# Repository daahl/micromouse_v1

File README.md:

# Micromouse_v1

This project aims to develop a [micromouse](https://www.youtube.com/results?search_query=micromouse) using a DOIT ESP32 dev module. The robot is powered by two 18620 batteries in series, and two micro metal motors fitted with encoders. The mapping is done using three VL53L0X TOF sensors.

**Currently a work in progress.**

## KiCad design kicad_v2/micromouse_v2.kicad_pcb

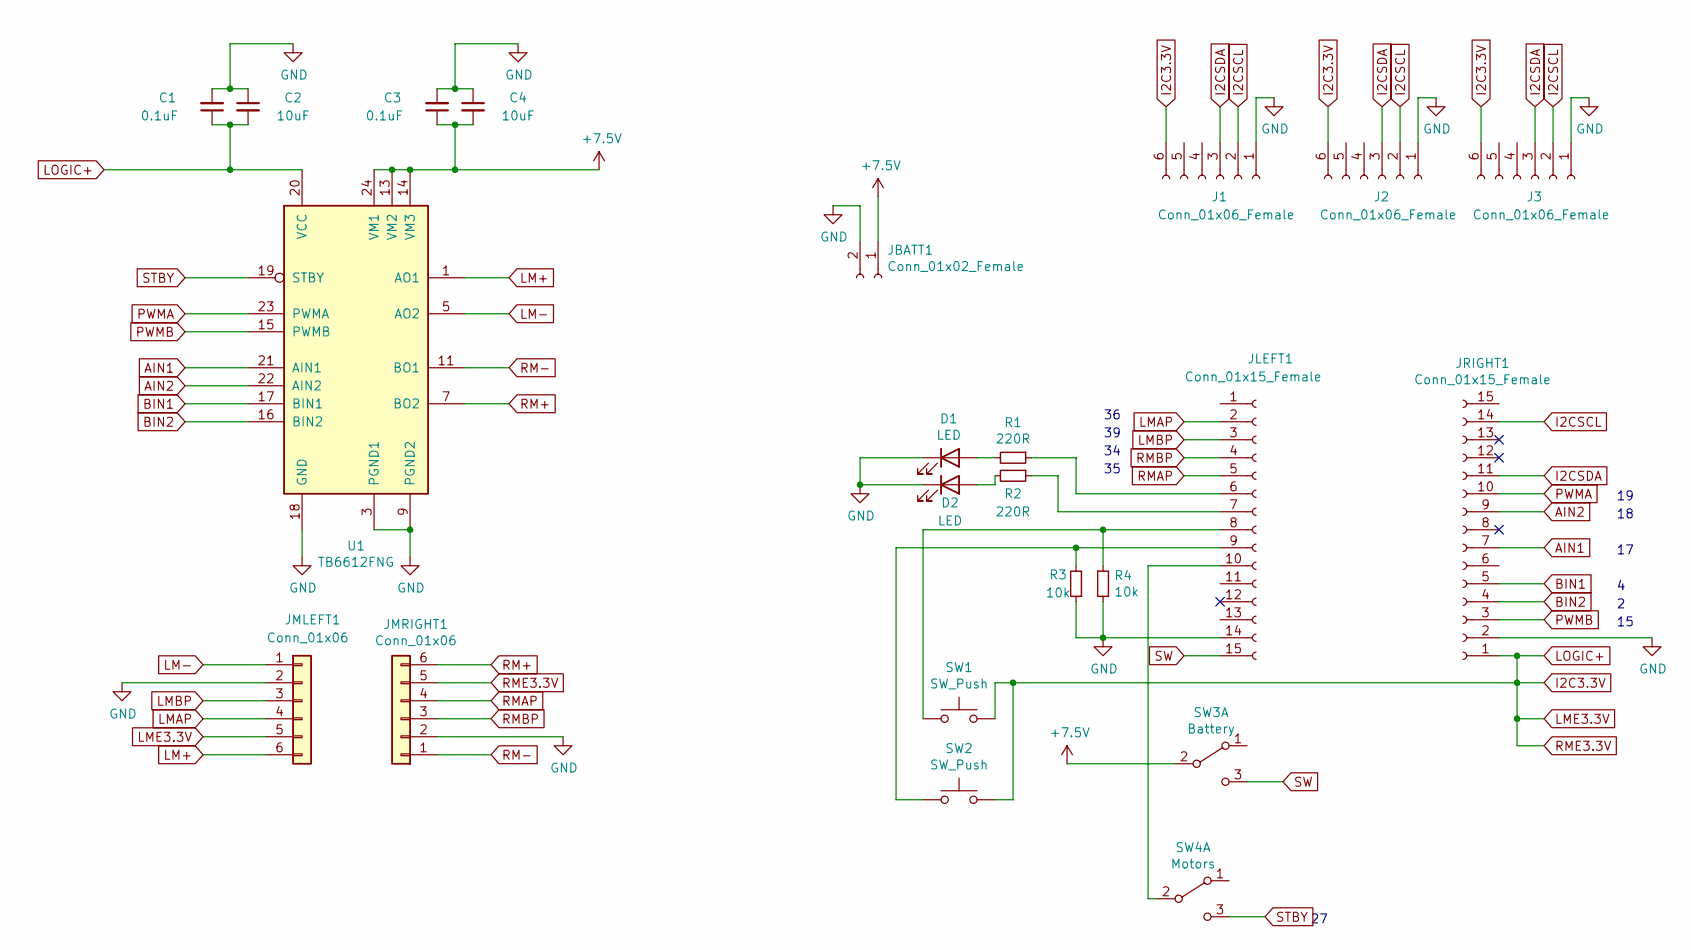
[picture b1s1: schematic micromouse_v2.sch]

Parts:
C1, C3: 0.1uF; C_0603_1608Metric_Pad1.08x0.95mm_HandSolder
C2, C4: 10uF; C_0603_1608Metric_Pad1.08x0.95mm_HandSolder
D1, D2: LED; LED_0603_1608Metric_Pad1.05x0.95mm_HandSolder
J1, J2, J3: Conn_01x06_Female; PinSocket_1x06_P2.54mm_Vertical
JBATT1: Conn_01x02_Female; JST_EH_B2B-EH-A_1x02_P2.50mm_Vertical
JLEFT1: Conn_01x15_Female; PinSocket_1x15_P2.54mm_Vertical
JMLEFT1: Conn_01x06; JST_EH_B6B-EH-A_1x06_P2.50mm_Vertical
JMRIGHT1: Conn_01x06; JST_EH_B6B-EH-A_1x06_P2.50mm_Vertical
JRIGHT1: Conn_01x15_Female; PinSocket_1x15_P2.54mm_Vertical
R1, R2: 220R; R_0603_1608Metric_Pad0.98x0.95mm_HandSolder
R3, R4: 10k; R_0603_1608Metric_Pad0.98x0.95mm_HandSolder
SW1, SW2: SW_Push; SW_SPST_Omron_B3FS-100xP
SW3: Battery; SW_CuK_OS102011MA1QN1_SPDT_Angled
SW4: Motors; SW_CuK_OS102011MA1QN1_SPDT_Angled
U1: TB6612FNG; SSOP-24_5.3x8.2mm_P0.65mm

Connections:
+7.5V: C3.1, C4.2, JBATT1.1, SW3.2 (B), U1.13 (VM2), U1.14 (VM3), U1.24 (VM1)
AIN1: JRIGHT1.7, U1.21 (AIN1)
AIN2: JRIGHT1.9, U1.22 (AIN2)
BIN1: JRIGHT1.5, U1.17 (BIN1)
BIN2: JRIGHT1.4, U1.16 (BIN2)
GND: C1.2, C2.1, C3.2, C4.1, D1.1 (K), D2.1 (K), J1.1, J2.1, J3.1, JBATT1.2, JLEFT1.14, JMLEFT1.2, JMRIGHT1.2, JRIGHT1.2, R3.1, R4.2, U1.3 (PGND1), U1.4 (PGND1), U1.9 (PGND2), U1.10 (PGND2), U1.18 (GND)
I2C3.3V: C1.1, C2.2, J1.6, J2.6, J3.6, JMLEFT1.5, JMRIGHT1.5, JRIGHT1.1, SW1.2, SW2.2, U1.20 (VCC)
I2CSCL: J1.2, J2.2, J3.2, JRIGHT1.14
I2CSDA: J1.3, J2.3, J3.3, JRIGHT1.11
LM+: JMLEFT1.6, U1.1 (AO1), U1.2 (AO1)
LM-: JMLEFT1.1, U1.5 (AO2), U1.6 (AO2)
LMAP: JLEFT1.2, JMLEFT1.4
LMBP: JLEFT1.3, JMLEFT1.3
unnamed: D1.2 (A), R1.2
unnamed: D2.2 (A), R2.2
unnamed: JLEFT1.6, R1.1
unnamed: JLEFT1.7, R2.1
unnamed: JLEFT1.8, R4.1, SW1.1
unnamed: JLEFT1.9, R3.2, SW2.1
unnamed: JLEFT1.10, SW4.2 (B)
PWMA: JRIGHT1.10, U1.23 (PWMA)
PWMB: JRIGHT1.3, U1.15 (PWMB)
RM+: JMRIGHT1.6, U1.7 (BO2), U1.8 (BO2)
RM-: JMRIGHT1.1, U1.11 (BO1), U1.12 (BO1)
RMAP: JLEFT1.5, JMRIGHT1.4
RMBP: JLEFT1.4, JMRIGHT1.3
STBY: SW4.3 (C), U1.19 (STBY)
SW: JLEFT1.15, SW3.3 (C)

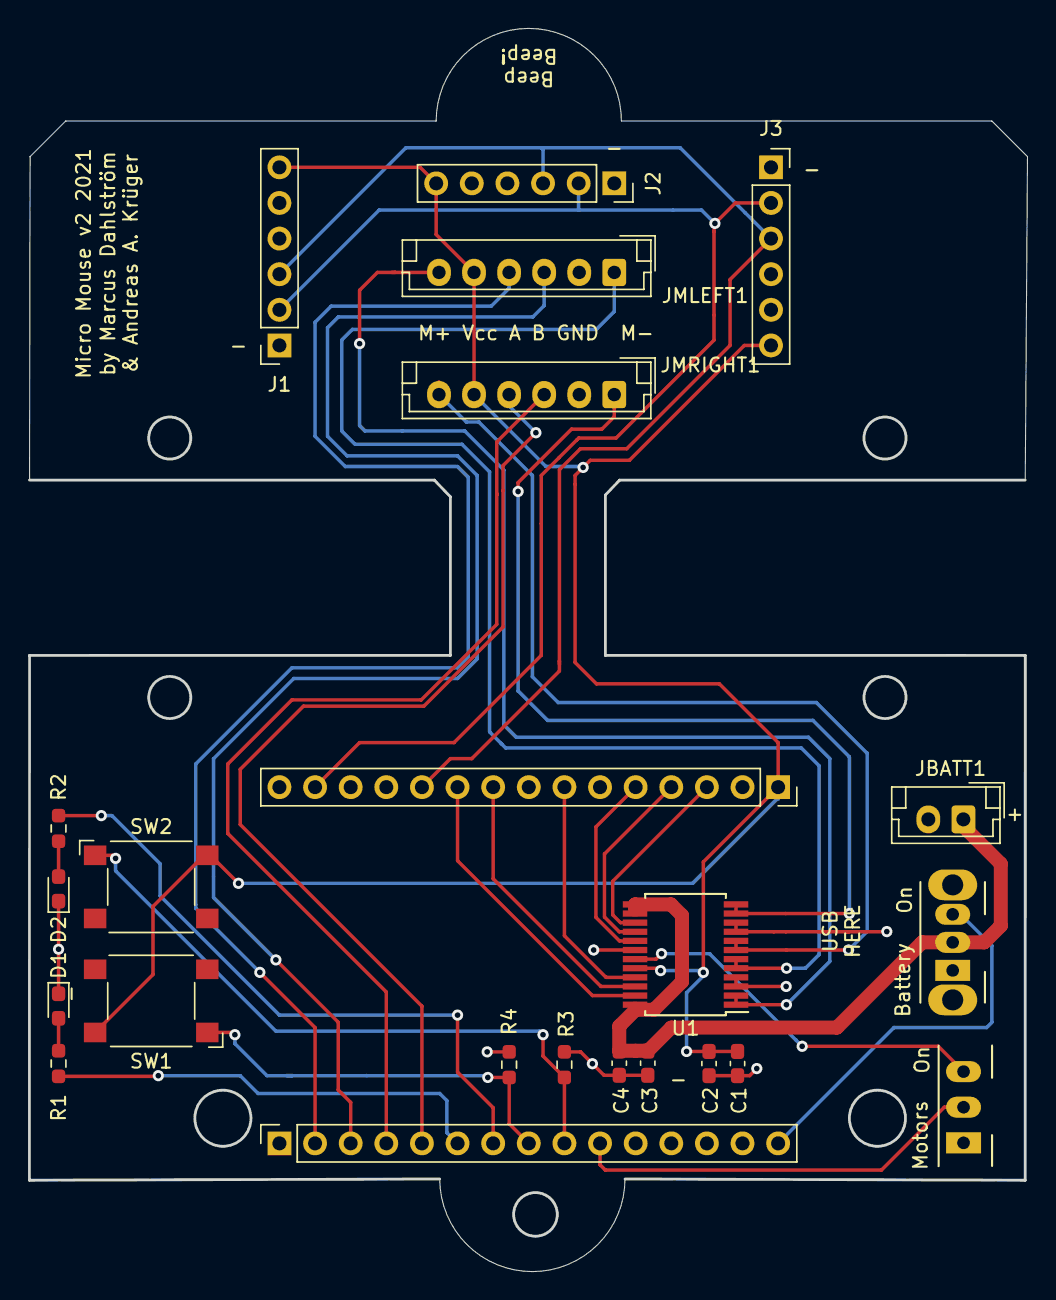
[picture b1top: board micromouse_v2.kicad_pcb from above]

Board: 2 copper layers, 71.1 x 88.5 mm, 23 parts (0 on the bottom side), 28 nets.

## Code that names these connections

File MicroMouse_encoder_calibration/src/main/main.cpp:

/*#include <Arduino.h>
#include "SparkFun_TB6612.h"

// Motor driver
#define AIN1    17
#define AIN2    18
#define PWMA    19
#define LOFFSET -1
#define BIN1    4
#define BIN2    2
#define PWMB    15
#define ROFFSET -1
#define STBY    27

// Motor encoders
#define encoderLLAA  36
#define encoderLLBB  39
#define encoderRRAA  35
#define encoderRRBB  34

// Motor objects to control the motors
Motor motorLL = Motor(AIN1, AIN2, PWMA, LOFFSET, STBY);
Motor motorRR = Motor(BIN1, BIN2, PWMB, ROFFSET, STBY);

// "Absolute" motor positions are set to 0 on startup
int absPosLL = 0;
int absPosRR = 0;

// acceleration parameters
float accLL = 0.0;
float accRR = 0.0;
float accLim = 0.75;
float deaccLim = 0.40;
float speedLim = 0.0;
float accSpeed = 3.0;
float deaccSpeed = 30.0;
int whineLim = 15;

// state varaibles
bool parked = 1;
bool accelerating = 0;
bool driving = 0;
bool deaccelerating = 0;
float distanceLim = 3.0;

// PID variables
int prevT = 0;
float eprevLL = 0.0;
float eprevRR = 0.0;
float eintegralLL = 0.0;
float eintegralRR = 0.0;
float speedLL = 0.0;
float speedRR = 0.0;

// define PID parameters
float kp = 7; //7
float kd = 0.1; //0.1
float ki = 0.0; //0

void readEncoderLL(){
  int b = digitalRead(encoderLLBB);
  // Add to pos on clockwise rotation
  if(b > 0){
    absPosLL--;
  }
  else{
    absPosLL++;
  }
}

void readEncoderRR(){
  int b = digitalRead(encoderRRBB);
  // Add to pos on counter clockwise rotation
  if(b > 0){
    absPosRR++;
  }
  else{
    absPosRR--;
  }
}

//
//  Return the absolute distance to the target.
//  0 = left motor
//  1 = right motor
//
float absDist2Target(int target, bool leftOrRight){
  if(leftOrRight)
  {
    return fabs(target - absPosRR);
  }else{
    return fabs(target - absPosLL);
  }
  
}

//
//  Regulates the speed to the motors. Has to be constantly called to regulate.
//
void PID(int targetLL, int targetRR){
  // time difference
  float currT = micros();
  float deltaT = ((float)(currT - prevT)/1.0e6);
  prevT = currT;

  // current error
  int eLL = targetLL - absPosLL;
  int eRR = targetRR - absPosRR;

  // derivative
  float dedtLL = (eLL - eprevLL)/deltaT;
  float dedtRR = (eRR - eprevRR)/deltaT;

  // integral
  eintegralLL = eintegralLL + eLL*deltaT;
  eintegralRR = eintegralRR + eRR*deltaT;

  // control signal
  float uLL = kp*eLL + kd*dedtLL + ki*eintegralLL;
  float uRR = kp*eRR + kd*dedtRR + ki*eintegralRR;

  // set and limit motor power
  speedLL = fabs(uLL);
  
  if(speedLL > speedLim){
    speedLL = speedLim;
  }
  speedRR = fabs(uRR);
  if(speedRR > speedLim){
    speedRR = speedLim;
  }

  // motor directions
  int dirLL = 1;
  if(uLL < 0){
    dirLL = -1;
  }
  int dirRR = 1;
  if(uRR < 0){
    dirRR = -1;
  }
  
  // store previous error
  eprevLL = eLL;
  eprevRR = eRR;

  // signal the motor
  motorLL.drive(dirLL*(int)speedLL);
  motorRR.drive(dirRR*(int)speedRR);

  // debug prints
  Serial.print("posLL:");
  Serial.print(absPosLL);
  Serial.print(",");
  Serial.print("posRR:");
  Serial.print(absPosRR);
  Serial.print(",");
  Serial.print("targetLL:");
  Serial.print(targetLL);
  Serial.print(",");
  Serial.print("targetRR:");
  Serial.println(targetRR);
}

//
//  State handling function to give the micromouse acceleration and deacceleration
//
void driveTo(int distanceLL, int distanceRR){
  float targetLL = absPosLL + distanceLL;
  float targetRR = absPosRR + distanceRR;

  // ### Parked state ### //
  while(parked){
    // too far away from target, change from parked to accelerating
    if(absDist2Target(targetLL, 0) > distanceLim or absDist2Target(targetRR, 1) > distanceLim){
    parked = 0;
    accelerating = 1;
    Serial.println("##### Accelerating #####");
    }
  }

  // ### Accelerating state ### //
  while(accelerating){
    if(speedLim < 255){
      speedLim += accSpeed;
    }
    PID(targetLL, targetRR);

    // accelerate until accLim% distance remains
    if((absDist2Target(targetLL, 0) <= accLim*fabs(distanceLL)) and (absDist2Target(targetRR, 1) <= accLim*fabs(distanceRR))){
      accelerating = 0;
      driving = 1;
      Serial.println("##### Driving #####");

      // short disances causes the speedLim to be too low,
      // minimum speed to move forward is 50.
      if(speedLim < 50){
        speedLim = 50;
      }
    }
  }

  // ### Driving state ### //
  while(driving){
    PID(targetLL, targetRR);

    // begin deaccelerating when deaccLim% distance remains
    if((absDist2Target(targetLL, 0) <= deaccLim*fabs(distanceLL)) and (absDist2Target(targetRR, 1) <= deaccLim*fabs(distanceRR))){
      driving = 0;
      deaccelerating = 1;
      Serial.println("##### Deaccelerating #####");
    }
  }

  // ### Deaccelerating state ### //
  while(deaccelerating){
    if(speedLim >= 70){
      speedLim -= deaccSpeed;
    }
    PID(targetLL, targetRR);

    // stop deaccelerating when close enough to target
    if(absDist2Target(targetLL, 0) <= distanceLim and absDist2Target(targetRR, 1) <= distanceLim){
      deaccelerating = 0;
      parked = 1;
      speedLim = 0.0;
      motorLL.brake();
      motorRR.brake();
      Serial.println("##### Parked #####");
    }
  }
}

void setup() {
  Serial.begin(115200);
  // Left motor encoder
  pinMode(encoderLLAA, INPUT);
  pinMode(encoderLLBB, INPUT);
  attachInterrupt(digitalPinToInterrupt(encoderLLAA), readEncoderLL, RISING);

  // Right motor encoder
  pinMode(encoderRRAA, INPUT);
  pinMode(encoderRRBB, INPUT);
  attachInterrupt(digitalPinToInterrupt(encoderRRAA), readEncoderRR, RISING);
  delay(4000);
}

void loop(){
    driveTo(500, 500);
    delay(700);
    driveTo(-345, +345);
    delay(700);
}*/
/*************************************************************

  This is a simple demo of sending and receiving some data.
  Be sure to check out other examples!
 *************************************************************/
//#include <Arduino.h>
#include <WiFi.h>
#include <WiFiClient.h>
#include <BlynkSimpleEsp32.h>
//#include "SparkFun_TB6612.h"

// Template ID, Device Name and Auth Token are provided by the Blynk.Cloud
// See the Device Info tab, or Template settings
#define BLYNK_TEMPLATE_ID "TMPLzIux-iXu"
#define BLYNK_DEVICE_NAME "Micromouse v2"
#define BLYNK_AUTH_TOKEN "2FeJeGJ-Ofr3sv2tWK5VPHD_gEaWwQE8"

// Comment this out to disable prints and save space
#define BLYNK_PRINT Serial

// Hardware pins
#define BOARD_LED_1 32

// Motor driver
#define AIN1    17
#define AIN2    18
#define PWMA    19
#define LOFFSET -1
#define BIN1    4
#define BIN2    2
#define PWMB    15
#define ROFFSET -1
#define STBY    27

// Motor objects and variables to control the motors
//Motor motorLL = Motor(AIN1, AIN2, PWMA, LOFFSET, STBY);
//Motor motorRR = Motor(BIN1, BIN2, PWMB, ROFFSET, STBY);
int speed = 0;
int turn = 0;

char auth[] = BLYNK_AUTH_TOKEN;

// Your WiFi credentials.
// Set password to "" for open networks.
char ssid[] = "Mulldalen";
char pass[] = "vilseiskogen";

BlynkTimer timer;

void driver(){
  //motorLL.drive(speed + turn);
  //motorRR.drive(speed - turn);
}

// Speed controller
BLYNK_WRITE(V0){
  int value = param.asInt();
  speed = value;
  driver();
}

// Turn controller
BLYNK_WRITE(V1){
  int value = param.asInt();
  turn = value;
  driver();
}

// LED controller. Is called everytime virtual pin 3 changes value
BLYNK_WRITE(V2)
{
  // Set incoming value from pin V0 to a variable
  int value = param.asInt();
  if(value == 1){
    digitalWrite(BOARD_LED_1, HIGH);
  }else{
    digitalWrite(BOARD_LED_1, LOW);
  }
}

// This function is called every time the device is connected to the Blynk.Cloud
BLYNK_CONNECTED()
{
  // Change Web Link Button message to "Congratulations!"
  Blynk.setProperty(V3, "offImageUrl", "https://static-image.nyc3.cdn.digitaloceanspaces.com/general/fte/congratulations.png");
  Blynk.setProperty(V3, "onImageUrl",  "https://static-image.nyc3.cdn.digitaloceanspaces.com/general/fte/congratulations_pressed.png");
  Blynk.setProperty(V3, "url", "https://docs.blynk.io/en/getting-started/what-do-i-need-to-blynk/how-quickstart-device-was-made");
}

// This function sends Arduino's uptime every second to Virtual Pin 2.

void myTimerEvent()
{
  // You can send any value at any time.
  // Please don't send more that 10 values per second.
  Blynk.virtualWrite(V2, millis() / 1000);
}

void setup()
{
  // Debug console and Blynk setup
  Serial.begin(115200);
  Blynk.begin(auth, ssid, pass);
  // You can also specify server:
  //Blynk.begin(auth, ssid, pass, "blynk.cloud", 80);
  //Blynk.begin(auth, ssid, pass, IPAddress(192,168,1,100), 8080);
  // Setup a function to be called every second
  timer.setInterval(1000L, myTimerEvent);

  // LED setup
  pinMode(BOARD_LED_1, OUTPUT);
}

void loop()
{
  Blynk.run();
  timer.run();
  // You can inject your own code or combine it with other sketches.
  // Check other examples on how to communicate with Blynk. Remember
  // to avoid delay() function!
}

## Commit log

2021-08-15 Add blink example
2022-08-07 Drive given distance fixed
2022-08-07 Add Blynk WiFi functions
2022-08-07 Motor functions but errors
